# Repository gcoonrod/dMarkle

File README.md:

<!--
 dMarkle (c) by Greg Coonrod
 
 dMarkle is licensed under a
 Creative Commons Attribution-ShareAlike 4.0 International License.
 
 You should have received a copy of the license along with this
 work. If not, see <http://creativecommons.org/licenses/by-sa/4.0/>.
-->

# dMarkle

A Raspberry Pi Pico based dice rolling toy.

## Usage

The dMarkle is programmed to roll one of any d4, d6, d8, d10, d12, d20, or d100 dice. The rotary encoder can be turned to select the die and then pushed to roll.

## Schematic and PCB

- Current [Schematic](./dMarkle-schematic-rev0.1.pdf)
- Current [PCB](./dMarkle-board-rev0.1.pdf)
  - The Pi Pico will be mounted on pin sockets. Hence the components that would otherwise be in an exclusion zone.

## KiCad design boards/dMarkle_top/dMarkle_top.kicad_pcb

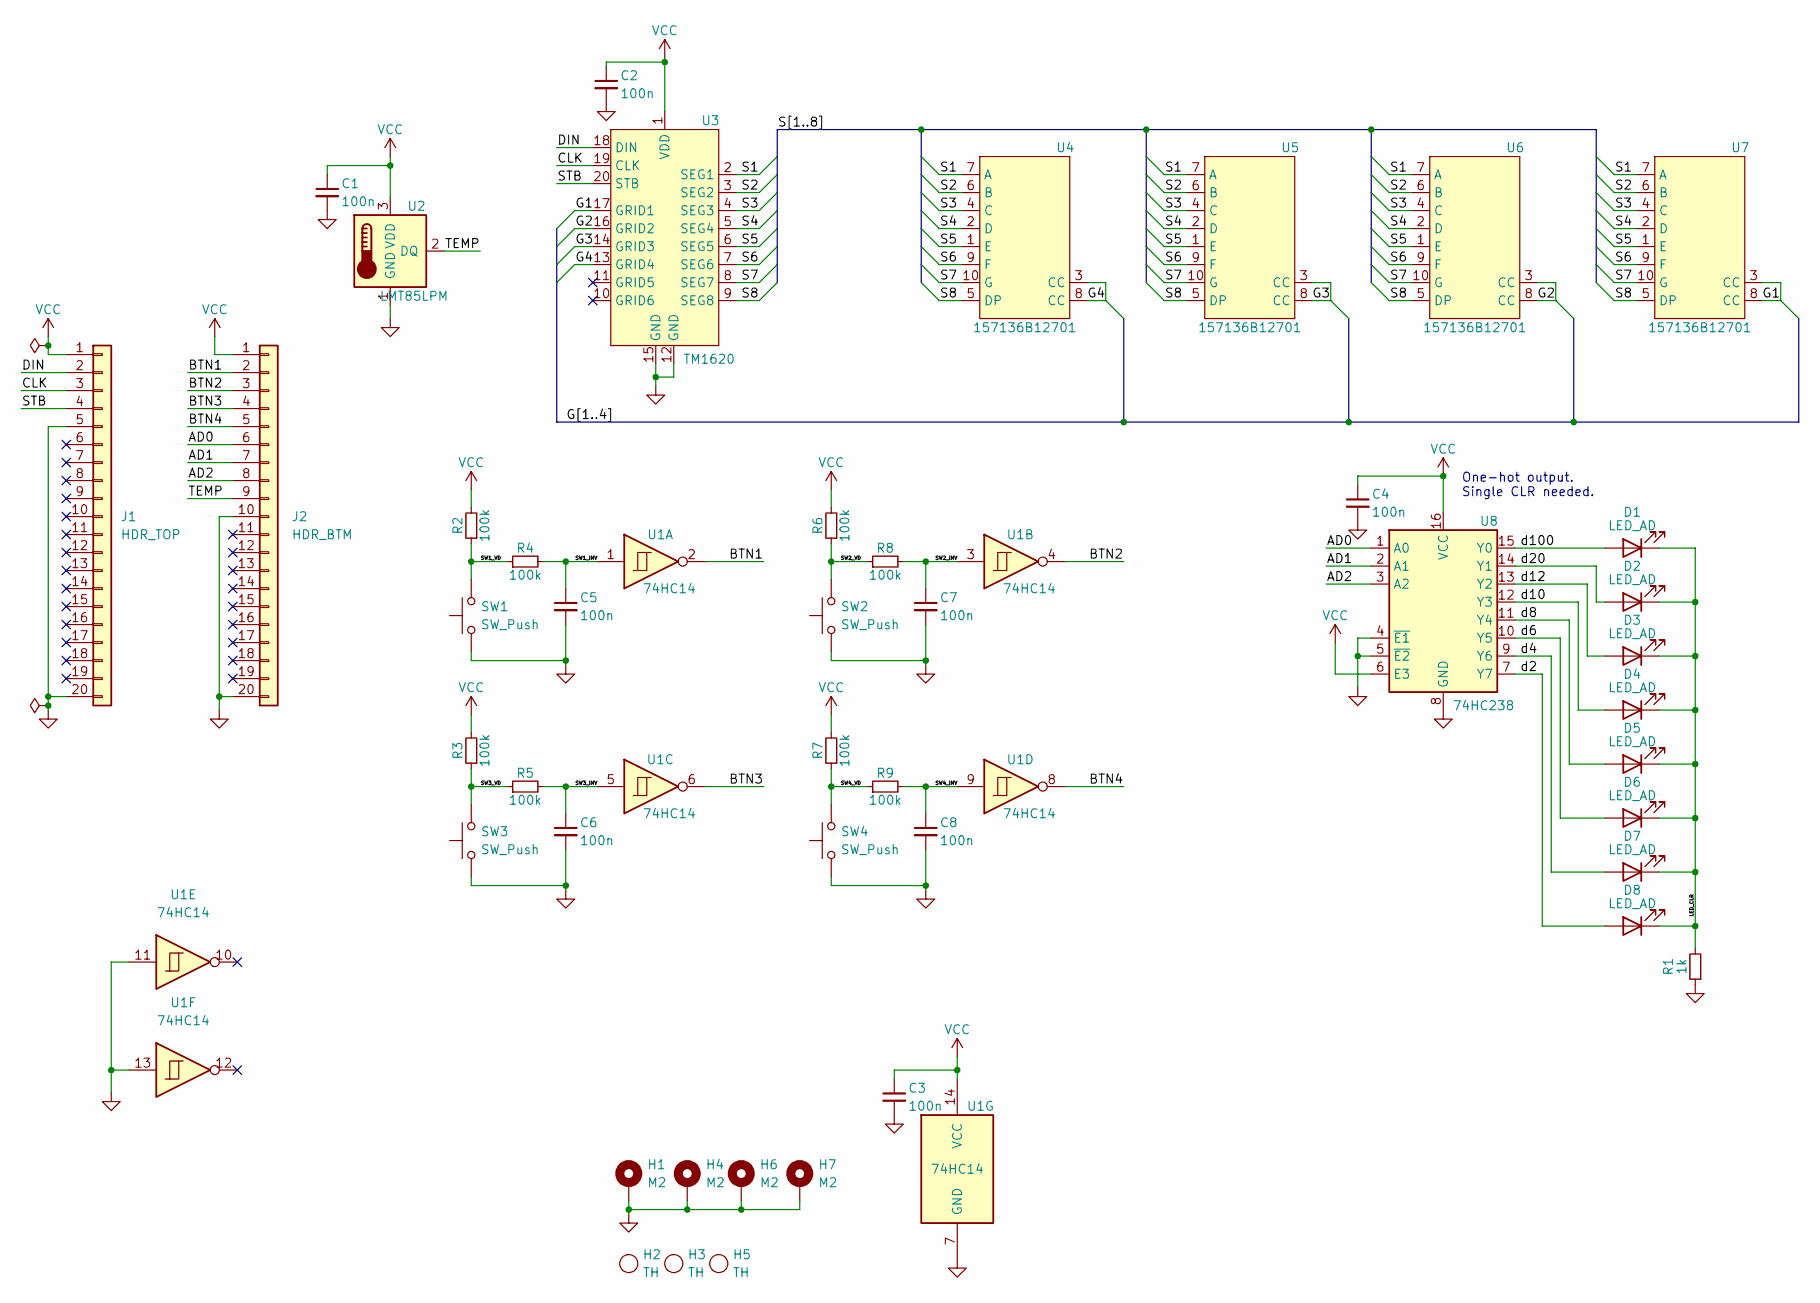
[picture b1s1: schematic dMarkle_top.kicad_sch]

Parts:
C1, C2, C3, C4, C5, C6, C7, C8: 100n; C_0603_1608Metric; Mfr Part CC0603KRX7R9BB104
D1, D2, D3, D4, D5, D6, D7, D8: LED_AD; LED_0603_1608Metric; Mfr Part C2290
H1, H4, H6, H7: M2; MountingHole_2.2mm_M2_Pad
H2, H3, H5: TH; ToolingHole
J1: HDR_TOP; PinHeader_1x20_P2.54mm_Vertical; Mfr Part 10129378-920001BLF
J2: HDR_BTM; PinHeader_1x20_P2.54mm_Vertical; Mfr Part M20-7822046
R1: 1k; R_0603_1608Metric; Mfr Part 0603WAF1001T5E
R2, R3, R4, R5, R6, R7, R8, R9: 100k; R_0603_1608Metric; Mfr Part 0603WAF1003T5E
SW1, SW2, SW3, SW4: SW_Push; SW_PUSH_6mm; Mfr Part TS02-66-73-BK-260-SCR-D
U1: 74HC14; DIP-14_W7.62mm_LongPads; Mfr Part TC74HC14APF
U2: LMT85LPM; TO-92_Inline; Mfr Part LMT85LPM
U3: TM1620; SOIC-20W_7.5x12.8mm_P1.27mm; Mfr Part TM1620
U4, U5, U6, U7: 157136B12701; Mfr Part 157136B12701
U8: 74HC238; DIP-16_W7.62mm_LongPads; Mfr Part CD74HC238E

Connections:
/AD0: J2.6, U8.1 (A0)
/AD1: J2.7, U8.2 (A1)
/AD2: J2.8, U8.3 (A2)
/BTN1: J2.2, U1.2
/BTN2: J2.3, U1.4
/BTN3: J2.4, U1.6
/BTN4: J2.5, U1.8
/CLK: J1.3, U3.19 (CLK)
/DIN: J1.2, U3.18 (DIN)
/G1: U3.17 (GRID1), U7.3 (CC), U7.8 (CC)
/G2: U3.16 (GRID2), U6.3 (CC), U6.8 (CC)
/G3: U3.14 (GRID3), U5.3 (CC), U5.8 (CC)
/G4: U3.13 (GRID4), U4.3 (CC), U4.8 (CC)
/LED_CLR: D1.1 (K), D2.1 (K), D3.1 (K), D4.1 (K), D5.1 (K), D6.1 (K), D7.1 (K), D8.1 (K), R1.2
/S1: U3.2 (SEG1), U4.7 (A), U5.7 (A), U6.7 (A), U7.7 (A)
/S2: U3.3 (SEG2), U4.6 (B), U5.6 (B), U6.6 (B), U7.6 (B)
/S3: U3.4 (SEG3), U4.4 (C), U5.4 (C), U6.4 (C), U7.4 (C)
/S4: U3.5 (SEG4), U4.2 (D), U5.2 (D), U6.2 (D), U7.2 (D)
/S5: U3.6 (SEG5), U4.1 (E), U5.1 (E), U6.1 (E), U7.1 (E)
/S6: U3.7 (SEG6), U4.9 (F), U5.9 (F), U6.9 (F), U7.9 (F)
/S7: U3.8 (SEG7), U4.10 (G), U5.10 (G), U6.10 (G), U7.10 (G)
/S8: U3.9 (SEG8), U4.5 (DP), U5.5 (DP), U6.5 (DP), U7.5 (DP)
/STB: J1.4, U3.20 (STB)
/SW1_INV: C5.1, R4.2, U1.1
/SW1_VD: R2.1, R4.1, SW1.2
/SW2_INV: C7.1, R8.2, U1.3
/SW2_VD: R6.1, R8.1, SW2.2
/SW3_INV: C6.1, R5.2, U1.5
/SW3_VD: R3.1, R5.1, SW3.2
/SW4_INV: C8.1, R9.2, U1.9
/SW4_VD: R7.1, R9.1, SW4.2
/TEMP: J2.9, U2.2 (DQ)
/d2: D8.2 (A), U8.7 (Y7)
/d4: D7.2 (A), U8.9 (Y6)
/d6: D6.2 (A), U8.10 (Y5)
/d8: D5.2 (A), U8.11 (Y4)
/d10: D4.2 (A), U8.12 (Y3)
/d12: D3.2 (A), U8.13 (Y2)
/d20: D2.2 (A), U8.14 (Y1)
/d100: D1.2 (A), U8.15 (Y0)
GND: C1.2, C2.2, C3.2, C4.2, C5.2, C6.2, C7.2, C8.2, H1.1, H4.1, H6.1, H7.1, J1.5, J1.20, J2.10, J2.20, R1.1, SW1.1, SW2.1, SW3.1, SW4.1, U1.7 (GND), U1.11, U1.13, U2.1 (GND), U3.12 (GND), U3.15 (GND), U8.4 (~E1), U8.5 (~E2), U8.8 (GND)
VCC: C1.1, C2.1, C3.1, C4.1, J1.1, J2.1, R2.2, R3.2, R6.2, R7.2, U1.14 (VCC), U2.3 (VDD), U3.1 (VDD), U8.6 (E3), U8.16 (VCC)

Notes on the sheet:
One-hot output. Single CLR needed.

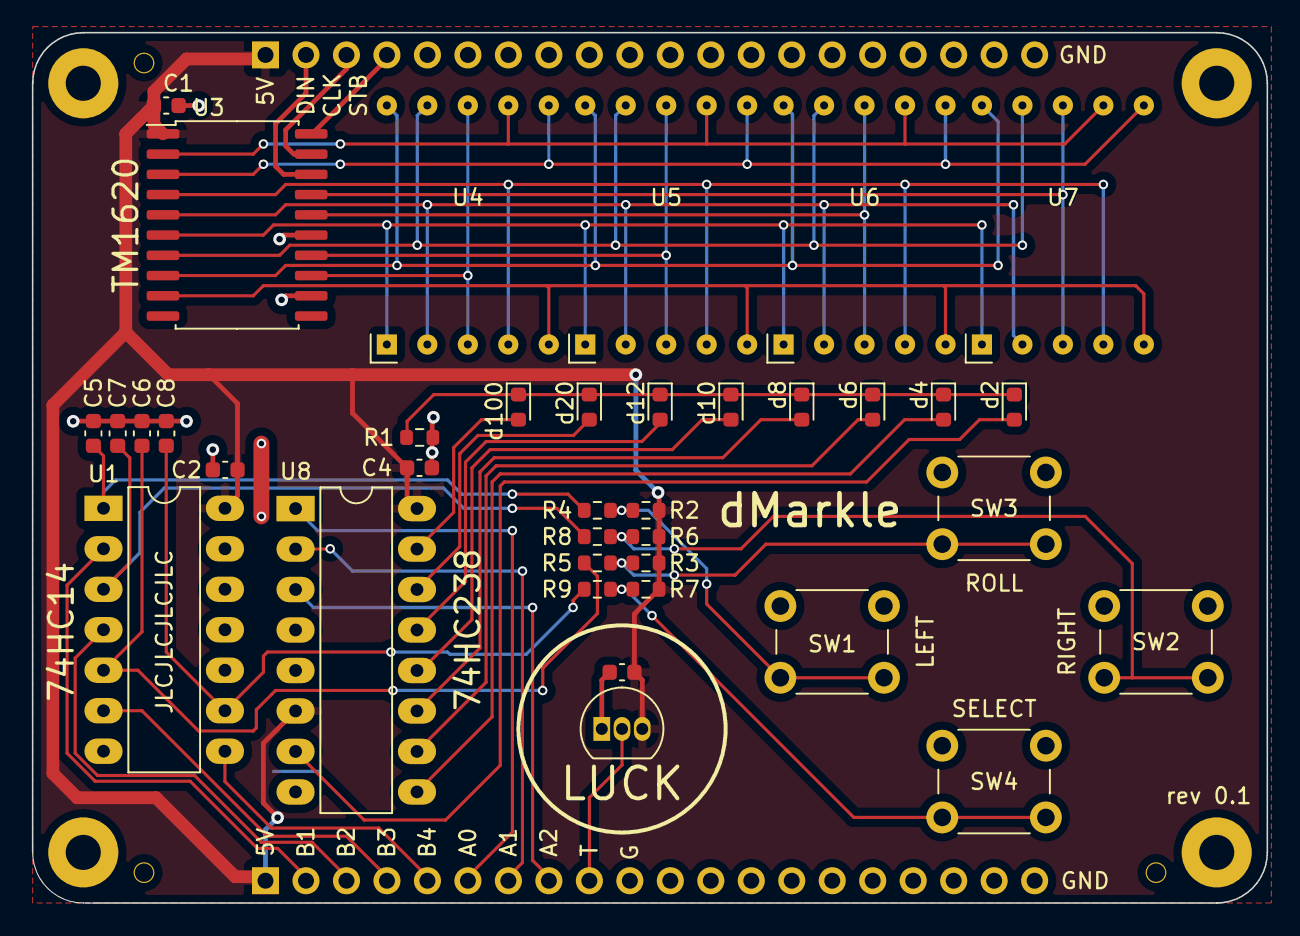
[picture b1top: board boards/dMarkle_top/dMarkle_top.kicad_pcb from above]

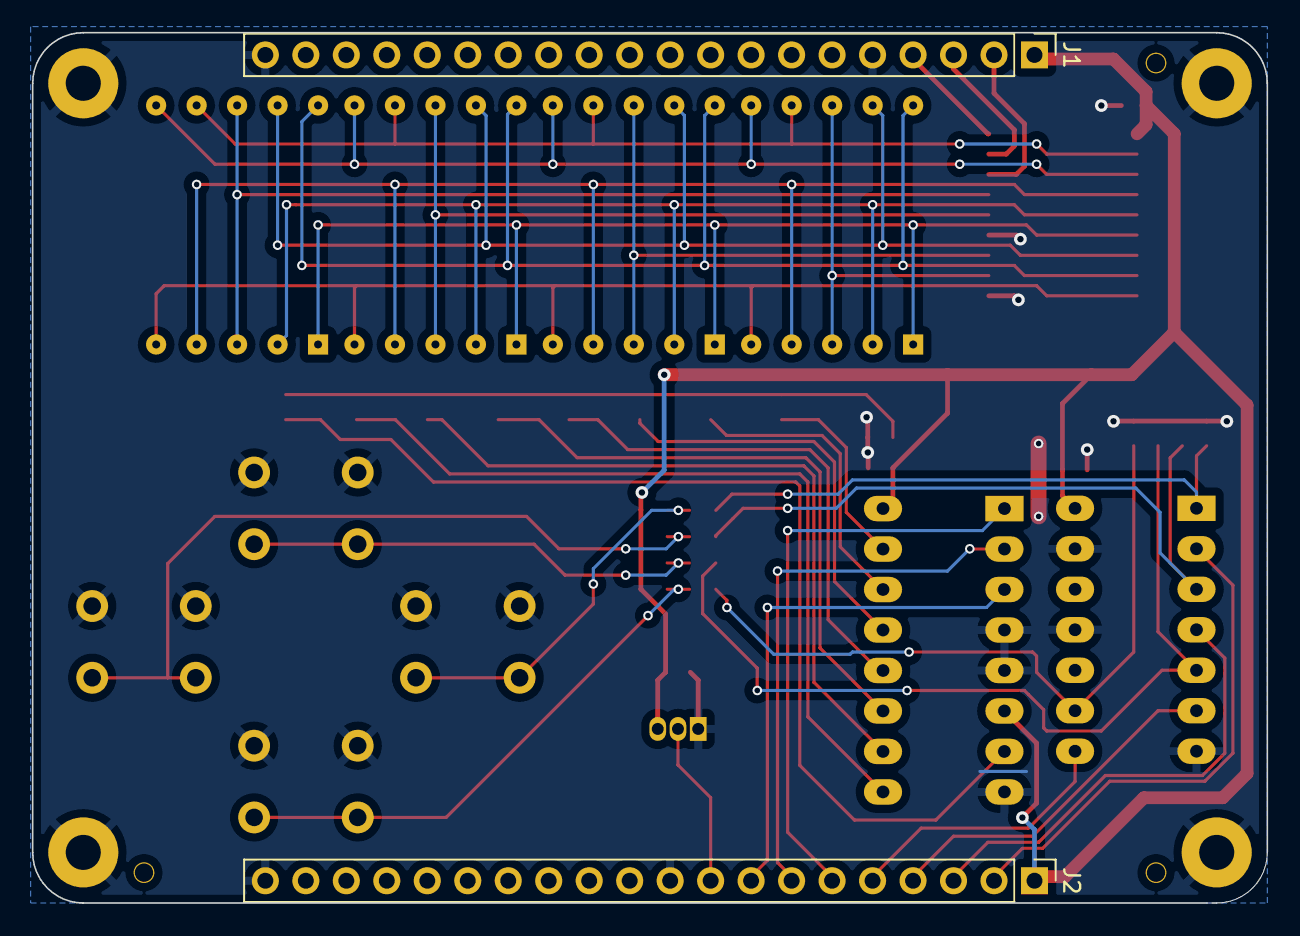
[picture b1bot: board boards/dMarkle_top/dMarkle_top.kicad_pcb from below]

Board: 2 copper layers, 77.5 x 54.6 mm, 46 parts (2 on the bottom side), 42 nets.

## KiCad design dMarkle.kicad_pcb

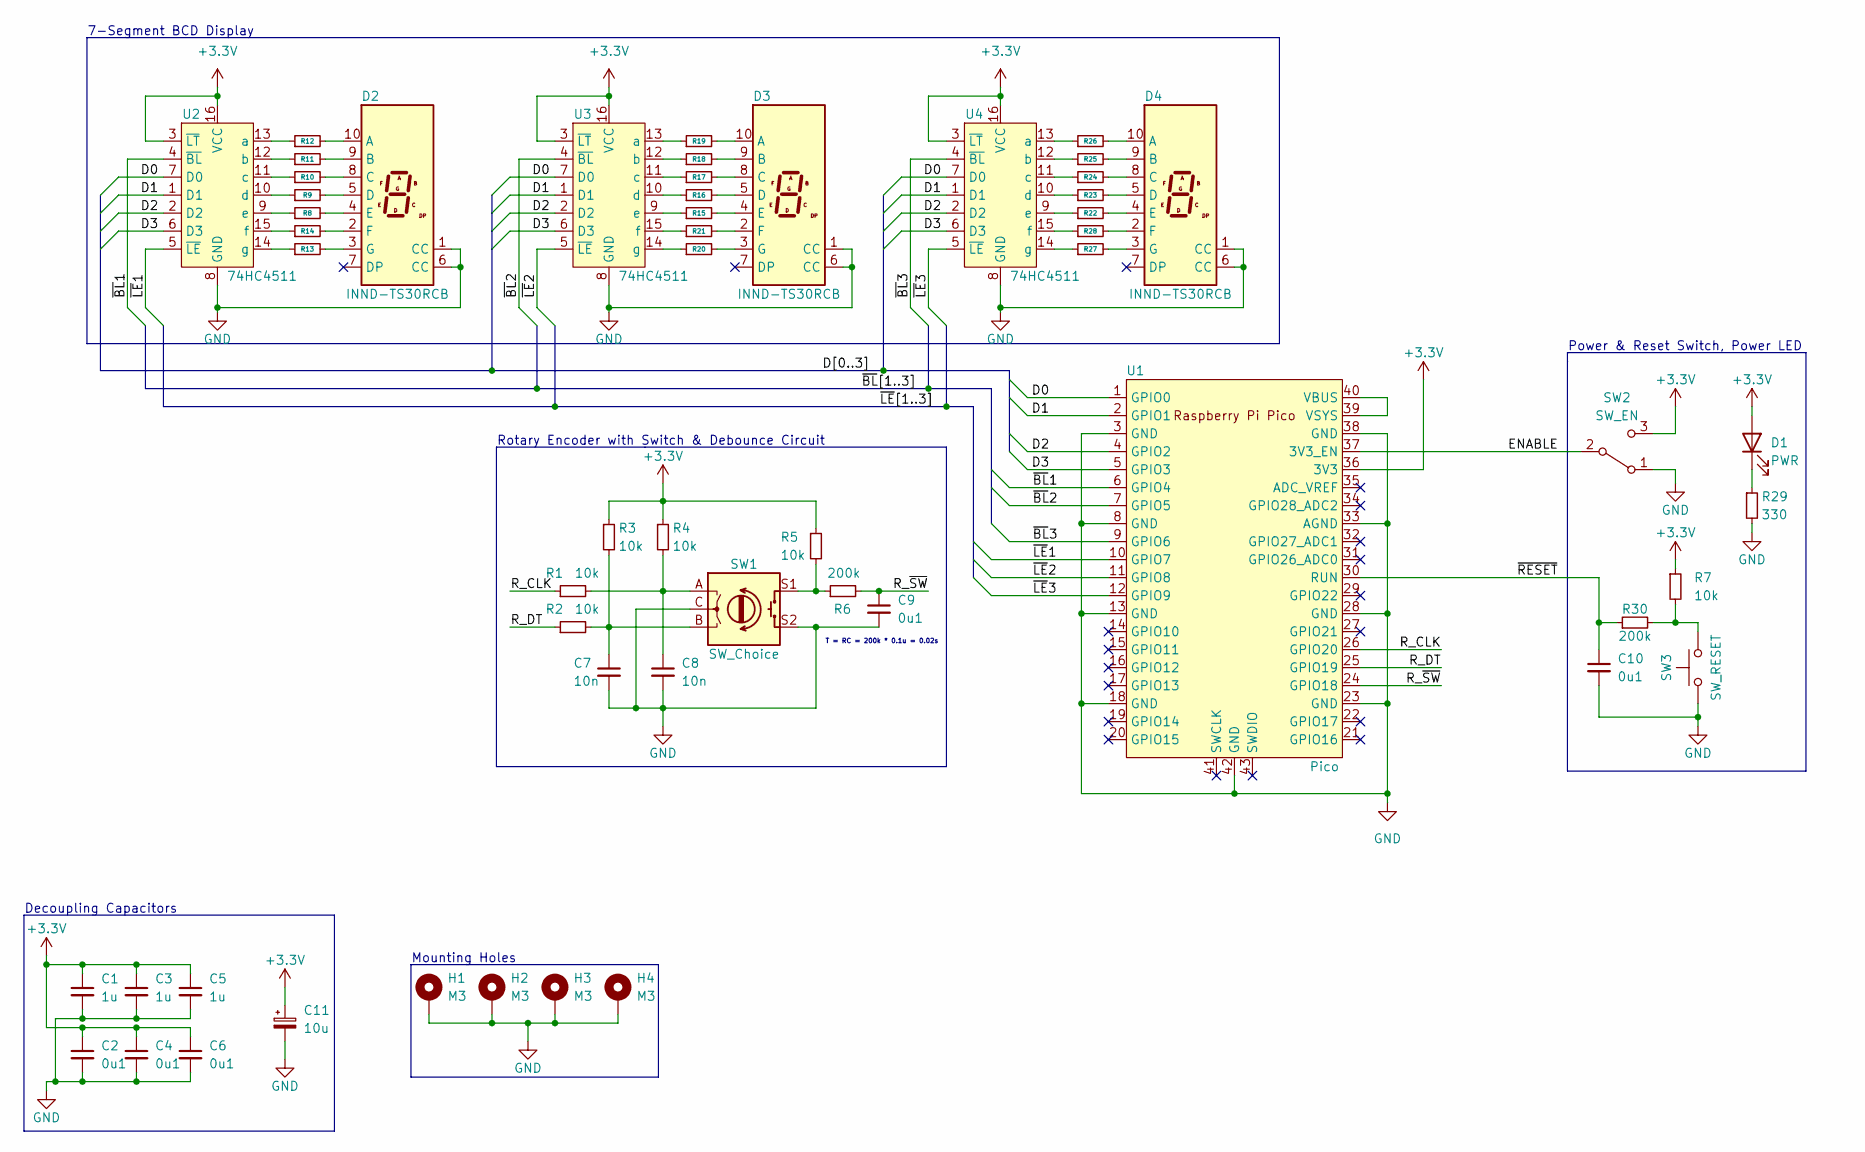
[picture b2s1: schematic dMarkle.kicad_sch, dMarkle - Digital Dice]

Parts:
C1, C3, C5: 1u; C_Rect_L4.0mm_W2.5mm_P2.50mm; Manufacturer Part Number FG18X5R1H105KRT06
C2, C4, C6, C9, C10: 0u1; C_Rect_L4.0mm_W2.5mm_P2.50mm; Manufacturer Part Number K104K15X7RF5TL2
C7, C8: 10n; C_Rect_L4.0mm_W2.5mm_P2.50mm; Manufacturer Part Number K103K15X7RF5TL2
C11: 10u; CP_Radial_D5.0mm_P2.00mm; Manufacturer Part Number 50YXM10MEFRTA5X11
D1: PWR; LED_D3.0mm; Manufacturer Part Number 151031SS04000
D2, D3, D4: INND-TS30RCB; HDSP-A151; Manufacturer Part Number INND-TS30RCB
H1, H2, H3, H4: M3; MountingHole_3.2mm_M3_Pad
R1, R2, R3, R4, R5, R7: 10k; R_Axial_DIN0204_L3.6mm_D1.6mm_P5.08mm_Horizontal; Manufacturer Part Number MBA02040C1002FRP00
R6, R30: 200k; R_Axial_DIN0204_L3.6mm_D1.6mm_P5.08mm_Horizontal; Manufacturer Part Number MBA02040C2003FCT00
R8, R9, R10, R11, R12, R13, R14, R15, R16, R17, R18, R19, R20, R21, R22, R23, R24, R25, R26, R27, R28, R29: 330; R_Axial_DIN0204_L3.6mm_D1.6mm_P5.08mm_Horizontal; Manufacturer Part Number MBA02040C3300FCT00
SW1: SW_Choice; RotaryEncoder_Alps_EC11E-Switch_Vertical_H20mm; Manufacturer Part Number PEC12R-4220F-S0024
SW2: SW_EN; SW_CuK_OS102011MA1QN1_SPDT_Angled; Manufacturer Part Number OS102011MA1QN1
SW3: SW_RESET; SW_PUSH_6mm; Manufacturer Part Number TL1105F160Q
U1: Pico; RPi_Pico_SMD_TH; Manufacturer Part Number SC0917
U2, U3, U4: 74HC4511; DIP-16_W7.62mm; Manufacturer Part Number CD74HC4511E

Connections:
+3.3V: C1.1, C2.1, C3.1, C4.1, C5.1, C6.1, C11.1, D1.2 (A), R3.1, R4.1, R5.1, R7.1, SW2.3 (C), U1.36 (3V3), U2.3 (~LT), U2.16 (VCC), U3.3 (~LT), U3.16 (VCC), U4.3 (~LT), U4.16 (VCC)
/D0: U1.1 (GPIO0), U2.7 (D0), U3.7 (D0), U4.7 (D0)
/D1: U1.2 (GPIO1), U2.1 (D1), U3.1 (D1), U4.1 (D1)
/D2: U1.4 (GPIO2), U2.2 (D2), U3.2 (D2), U4.2 (D2)
/D3: U1.5 (GPIO3), U2.6 (D3), U3.6 (D3), U4.6 (D3)
/ENABLE: SW2.2 (B), U1.37 (3V3_EN)
/R_CLK: R1.1, U1.26 (GPIO20)
/R_DT: R2.1, U1.25 (GPIO19)
/R_~SW: C9.1, R6.2, U1.24 (GPIO18)
/~BL1: U1.6 (GPIO4), U2.4 (~BL)
/~BL2: U1.7 (GPIO5), U3.4 (~BL)
/~BL3: U1.9 (GPIO6), U4.4 (~BL)
/~LE1: U1.10 (GPIO7), U2.5 (~LE)
/~LE2: U1.11 (GPIO8), U3.5 (~LE)
/~LE3: U1.12 (GPIO9), U4.5 (~LE)
/~RESET: C10.1, R30.1, U1.30 (RUN)
GND: C1.2, C2.2, C3.2, C4.2, C5.2, C6.2, C7.2, C8.2, C9.2, C10.2, C11.2, D2.1 (CC), D2.6 (CC), D3.1 (CC), D3.6 (CC), D4.1 (CC), D4.6 (CC), H1.1, H2.1, H3.1, H4.1, R29.2, SW1.C, SW1.S2, SW2.1 (A), SW3.1, U1.3 (GND), U1.8 (GND), U1.13 (GND), U1.18 (GND), U1.23 (GND), U1.28 (GND), U1.33 (AGND), U1.38 (GND), U1.42 (GND), U2.8 (GND), U3.8 (GND), U4.8 (GND)
unnamed: C7.1, R2.2, R3.2, SW1.B
unnamed: C8.1, R1.2, R4.2, SW1.A
unnamed: D1.1 (K), R29.1
unnamed: D2.2 (F), R14.2
unnamed: D2.3 (G), R13.2
unnamed: D2.4 (E), R8.2
unnamed: D2.5 (D), R9.2
unnamed: D2.8 (C), R10.2
unnamed: D2.9 (B), R11.2
unnamed: D2.10 (A), R12.2
unnamed: D3.2 (F), R21.2
unnamed: D3.3 (G), R20.2
unnamed: D3.4 (E), R15.2
unnamed: D3.5 (D), R16.2
unnamed: D3.8 (C), R17.2
unnamed: D3.9 (B), R18.2
unnamed: D3.10 (A), R19.2
unnamed: D4.2 (F), R28.2
unnamed: D4.3 (G), R27.2
unnamed: D4.4 (E), R22.2
unnamed: D4.5 (D), R23.2
unnamed: D4.8 (C), R24.2
unnamed: D4.9 (B), R25.2
unnamed: D4.10 (A), R26.2
unnamed: R5.2, R6.1, SW1.S1
unnamed: R8.1, U2.9 (e)
unnamed: R9.1, U2.10 (d)
unnamed: R10.1, U2.11 (c)
unnamed: R11.1, U2.12 (b)
unnamed: R12.1, U2.13 (a)
unnamed: R13.1, U2.14 (g)
unnamed: R14.1, U2.15 (f)
unnamed: R15.1, U3.9 (e)
unnamed: R16.1, U3.10 (d)
unnamed: R17.1, U3.11 (c)
unnamed: R18.1, U3.12 (b)
unnamed: R19.1, U3.13 (a)
unnamed: R20.1, U3.14 (g)
unnamed: R21.1, U3.15 (f)
unnamed: R22.1, U4.9 (e)
unnamed: R23.1, U4.10 (d)
unnamed: R24.1, U4.11 (c)
unnamed: R25.1, U4.12 (b)
unnamed: R26.1, U4.13 (a)
unnamed: R27.1, U4.14 (g)
unnamed: R28.1, U4.15 (f)
unnamed: R7.2, R30.2, SW3.2
unnamed: U1.39 (VSYS), U1.40 (VBUS)

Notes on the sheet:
Decoupling Capacitors
Rotary Encoder with Switch & Debounce Circuit
7-Segment BCD Display
T = RC = 200k * 0.1u = 0.02s
Mounting Holes
Power & Reset Switch, Power LED

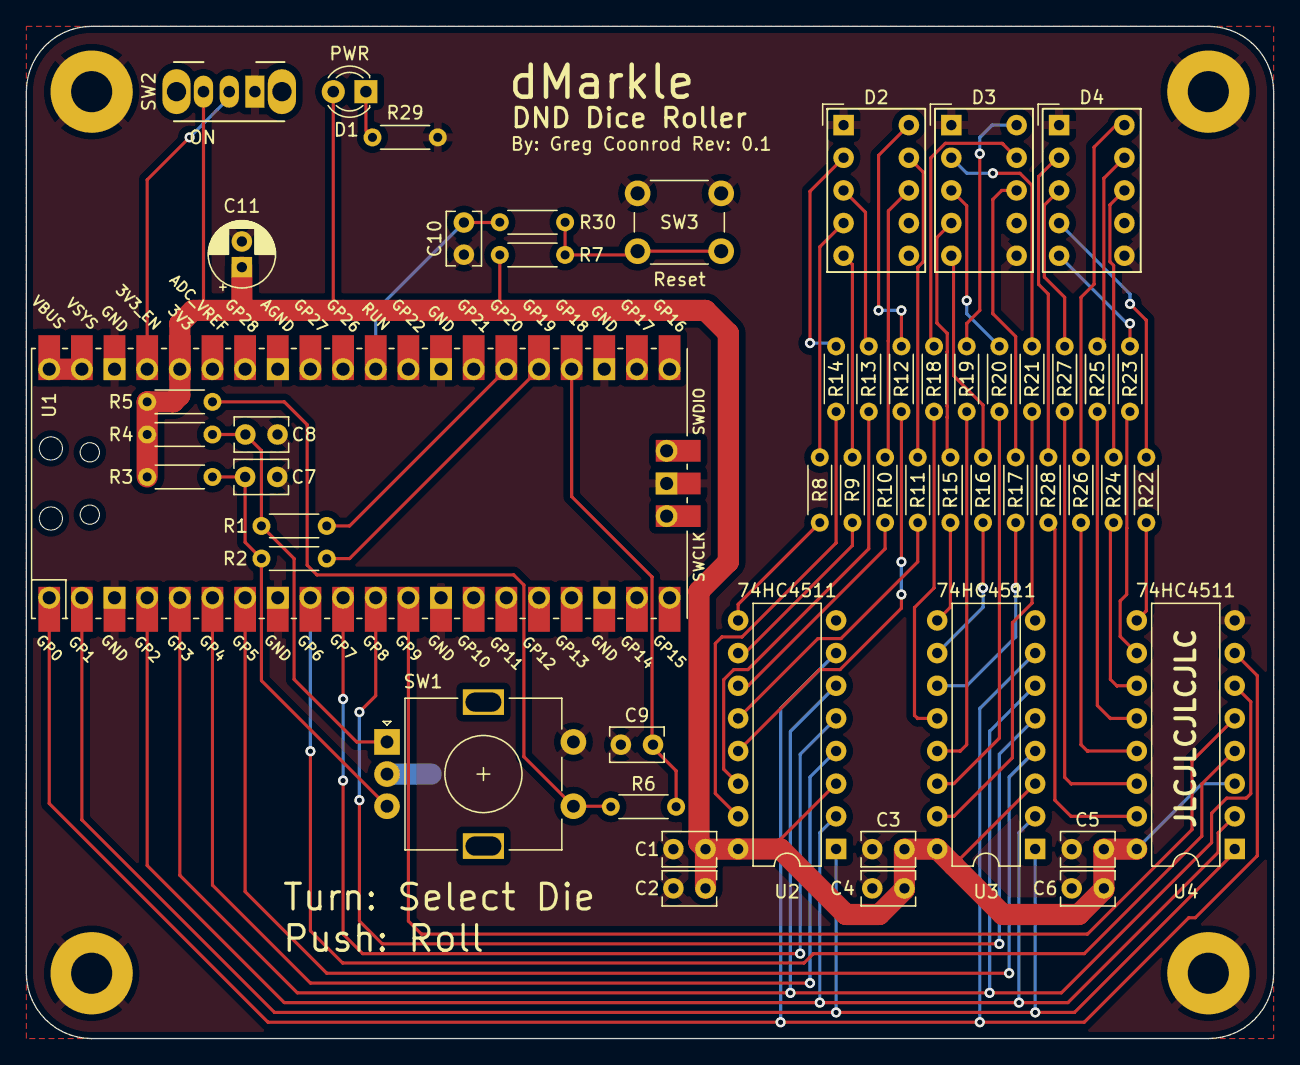
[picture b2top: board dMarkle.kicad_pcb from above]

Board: 2 copper layers, 97.0 x 78.7 mm, 56 parts (0 on the bottom side), 65 nets.

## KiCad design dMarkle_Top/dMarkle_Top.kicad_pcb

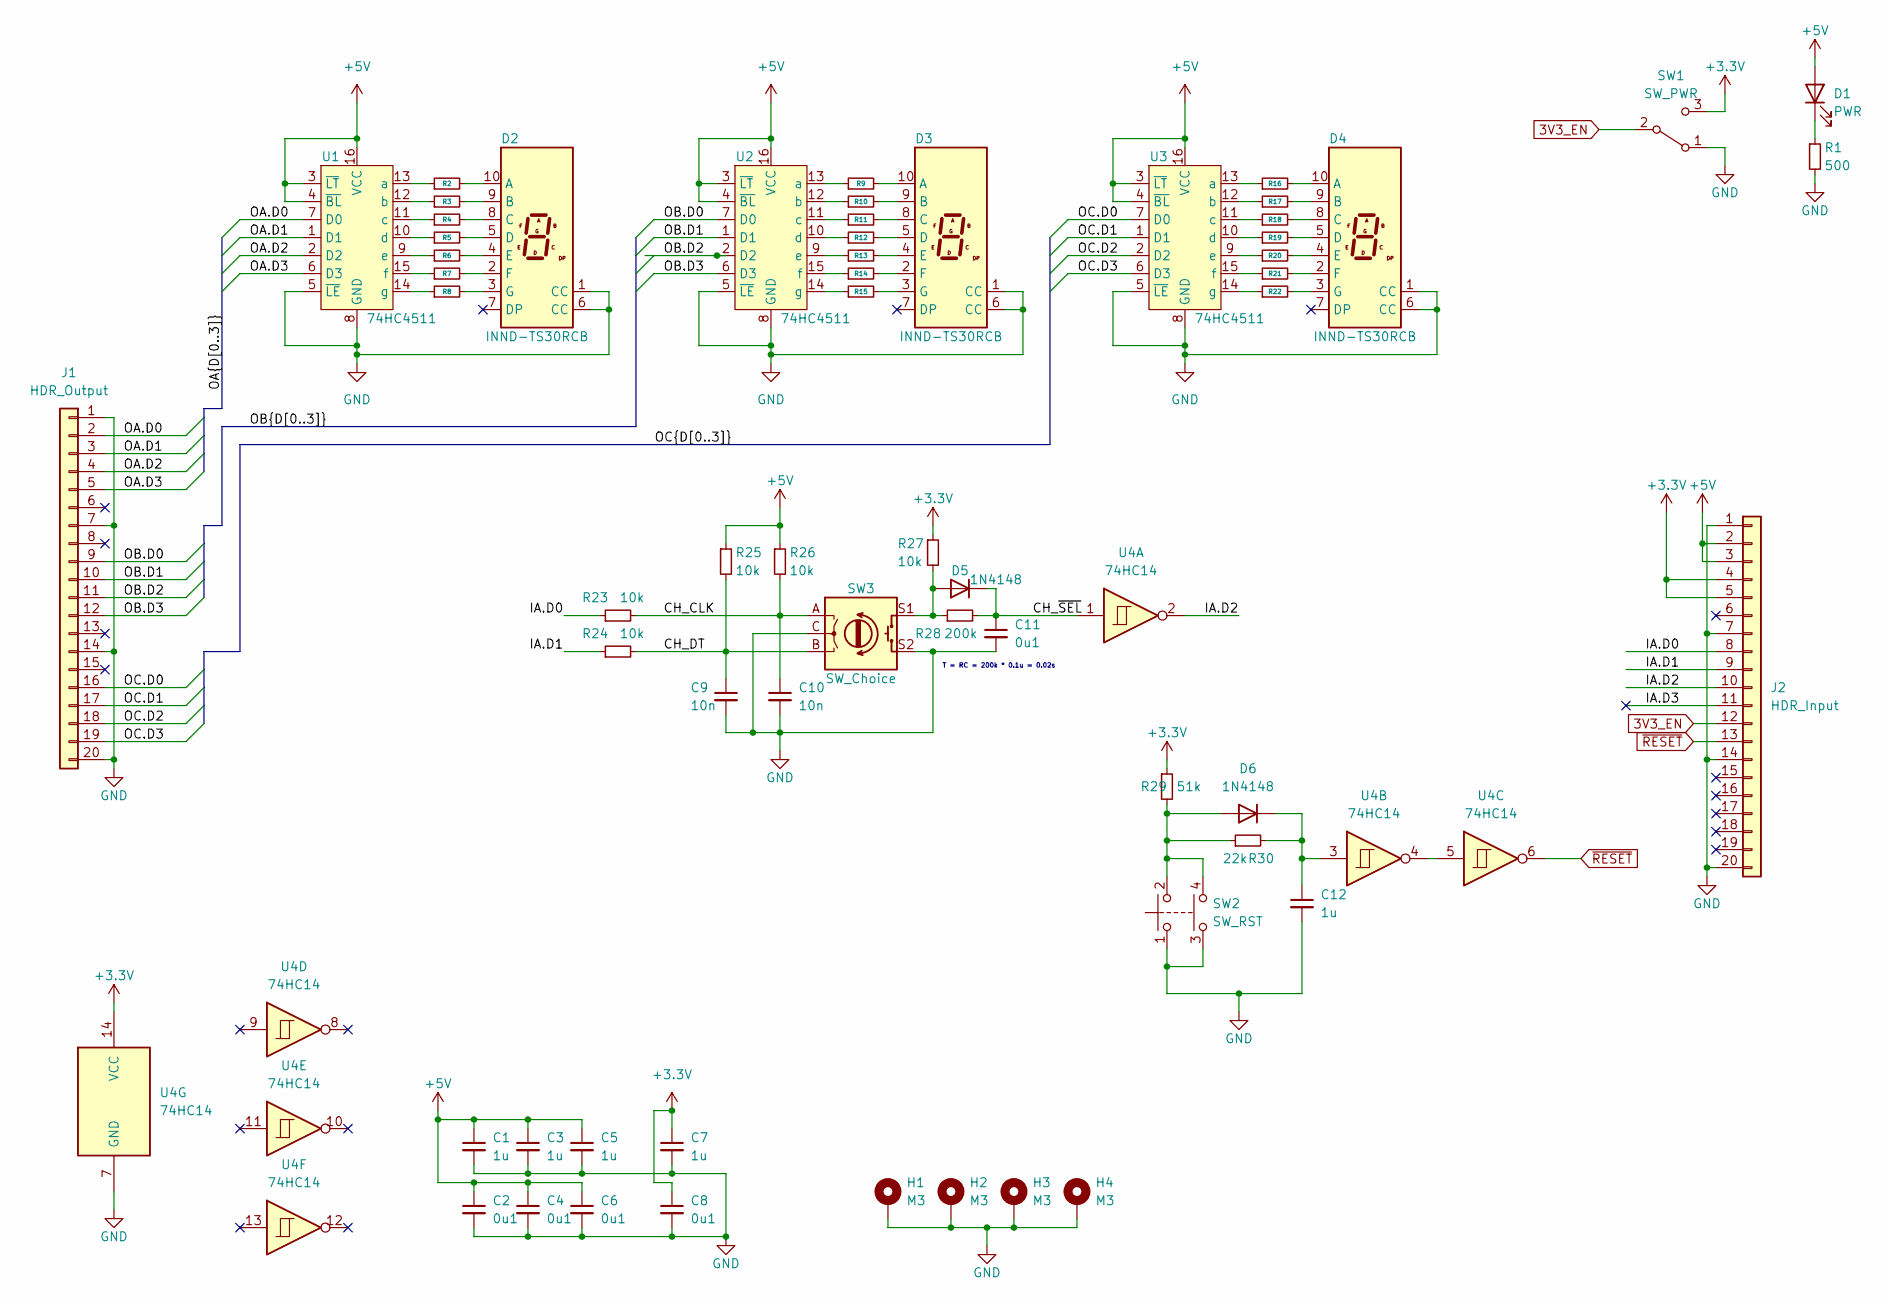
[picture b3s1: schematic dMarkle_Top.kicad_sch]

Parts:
C1, C3, C5, C7, C12: 1u; C_Rect_L4.0mm_W2.5mm_P2.50mm
C2, C4, C6, C8, C11: 0u1; C_Rect_L4.0mm_W2.5mm_P2.50mm
C9, C10: 10n; C_Rect_L4.0mm_W2.5mm_P2.50mm
D1: PWR; LED_D3.0mm
D2, D3, D4: INND-TS30RCB; HDSP-A151
D5, D6: 1N4148; D_DO-35_SOD27_P7.62mm_Horizontal
H1, H2, H3, H4: M3; MountingHole_3.2mm_M3_Pad
J1: HDR_Output; PinSocket_1x20_P2.54mm_Vertical
J2: HDR_Input; PinSocket_1x20_P2.54mm_Vertical
R1: 500; R_Axial_DIN0204_L3.6mm_D1.6mm_P5.08mm_Horizontal
R2, R3, R4, R5, R6, R7, R8, R9, R10, R11, R12, R13, R14, R15, R16, R17, R18, R19, R20, R21, R22: 330; R_Axial_DIN0204_L3.6mm_D1.6mm_P5.08mm_Horizontal
R23, R24, R25, R26, R27: 10k; R_Axial_DIN0204_L3.6mm_D1.6mm_P5.08mm_Horizontal
R28: 200k; R_Axial_DIN0204_L3.6mm_D1.6mm_P5.08mm_Horizontal
R29: 51k; R_Axial_DIN0204_L3.6mm_D1.6mm_P5.08mm_Horizontal
R30: 22k; R_Axial_DIN0204_L3.6mm_D1.6mm_P5.08mm_Horizontal
SW1: SW_PWR; SW_Slide_1P2T_CK_OS102011MS2Q
SW2: SW_RST; SW_Tactile_Straight_KSA0Axx1LFTR
SW3: SW_Choice; RotaryEncoder_Alps_EC11E-Switch_Vertical_H20mm; Manufacturer Part Number PEC12R-4220F-S0024
U1, U2, U3: 74HC4511; DIP-16_W7.62mm
U4: 74HC14; DIP-14_W7.62mm_Socket

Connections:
3V3_EN: J2.12, SW1.2 (B)
+5V: C1.1, C2.1, C3.1, C4.1, C5.1, C6.1, D1.2 (A), J2.2, J2.3, R25.1, R26.1, U1.3 (~LT), U1.4 (~BL), U1.16 (VCC), U2.3 (~LT), U2.4 (~BL), U2.16 (VCC), U3.3 (~LT), U3.4 (~BL), U3.16 (VCC)
/CH_CLK: C10.1, R23.2, R26.2, SW3.A
/CH_DT: C9.1, R24.2, R25.2, SW3.B
/CH_~SEL: C11.1, D5.1 (K), R28.2, U4.1
/IA.D0: J2.8, R23.1
/IA.D1: J2.9, R24.1
/IA.D2: J2.10, U4.2
/IA.D3: J2.11
/OA.D0: J1.2, U1.7 (D0)
/OA.D1: J1.3, U1.1 (D1)
/OA.D2: J1.4, U1.2 (D2)
/OA.D3: J1.5, U1.6 (D3)
/OB.D0: J1.9, U2.7 (D0)
/OB.D1: J1.10, U2.1 (D1)
/OB.D2: J1.11, U2.2 (D2)
/OB.D3: J1.12, U2.6 (D3)
/OC.D0: J1.16, U3.7 (D0)
/OC.D1: J1.17, U3.1 (D1)
/OC.D2: J1.18, U3.2 (D2)
/OC.D3: J1.19, U3.6 (D3)
GND: C1.2, C2.2, C3.2, C4.2, C5.2, C6.2, C7.2, C8.2, C9.2, C10.2, C11.2, C12.2, D2.1 (CC), D2.6 (CC), D3.1 (CC), D3.6 (CC), D4.1 (CC), D4.6 (CC), H1.1, H2.1, H3.1, H4.1, J1.1, J1.7, J1.14, J1.20, J2.1, J2.7, J2.14, J2.20, R1.2, SW1.1 (A), SW2.1, SW2.3, SW3.C, SW3.S2, U1.5 (~LE), U1.8 (GND), U2.5 (~LE), U2.8 (GND), U3.5 (~LE), U3.8 (GND), U4.7 (GND)
unnamed: D1.1 (K), R1.1
unnamed: D2.2 (F), R7.2
unnamed: D2.3 (G), R8.2
unnamed: D2.4 (E), R6.2
unnamed: D2.5 (D), R5.2
unnamed: D2.8 (C), R4.2
unnamed: D2.9 (B), R3.2
unnamed: D2.10 (A), R2.2
unnamed: D3.2 (F), R14.2
unnamed: D3.3 (G), R15.2
unnamed: D3.4 (E), R13.2
unnamed: D3.5 (D), R12.2
unnamed: D3.8 (C), R11.2
unnamed: D3.9 (B), R10.2
unnamed: D3.10 (A), R9.2
unnamed: D4.2 (F), R21.2
unnamed: D4.3 (G), R22.2
unnamed: D4.4 (E), R20.2
unnamed: D4.5 (D), R19.2
unnamed: D4.8 (C), R18.2
unnamed: D4.9 (B), R17.2
unnamed: D4.10 (A), R16.2
unnamed: D5.2 (A), R27.2, R28.1, SW3.S1
unnamed: D6.2 (A), R29.2, R30.1, SW2.2, SW2.4
unnamed: R6.1, U1.9 (e)
unnamed: R5.1, U1.10 (d)
unnamed: R4.1, U1.11 (c)
unnamed: R3.1, U1.12 (b)
unnamed: R2.1, U1.13 (a)
unnamed: R8.1, U1.14 (g)
unnamed: R7.1, U1.15 (f)
unnamed: R13.1, U2.9 (e)
unnamed: R12.1, U2.10 (d)
unnamed: R11.1, U2.11 (c)
unnamed: R10.1, U2.12 (b)
unnamed: R9.1, U2.13 (a)
unnamed: R15.1, U2.14 (g)
unnamed: R14.1, U2.15 (f)
unnamed: R20.1, U3.9 (e)
unnamed: R19.1, U3.10 (d)
unnamed: R18.1, U3.11 (c)
unnamed: R17.1, U3.12 (b)
unnamed: R16.1, U3.13 (a)
unnamed: R22.1, U3.14 (g)
unnamed: R21.1, U3.15 (f)
unnamed: C12.1, D6.1 (K), R30.2, U4.3
unnamed: U4.4, U4.5
~RESET: J2.13, U4.6

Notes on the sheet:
T = RC = 200k * 0.1u = 0.02s

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
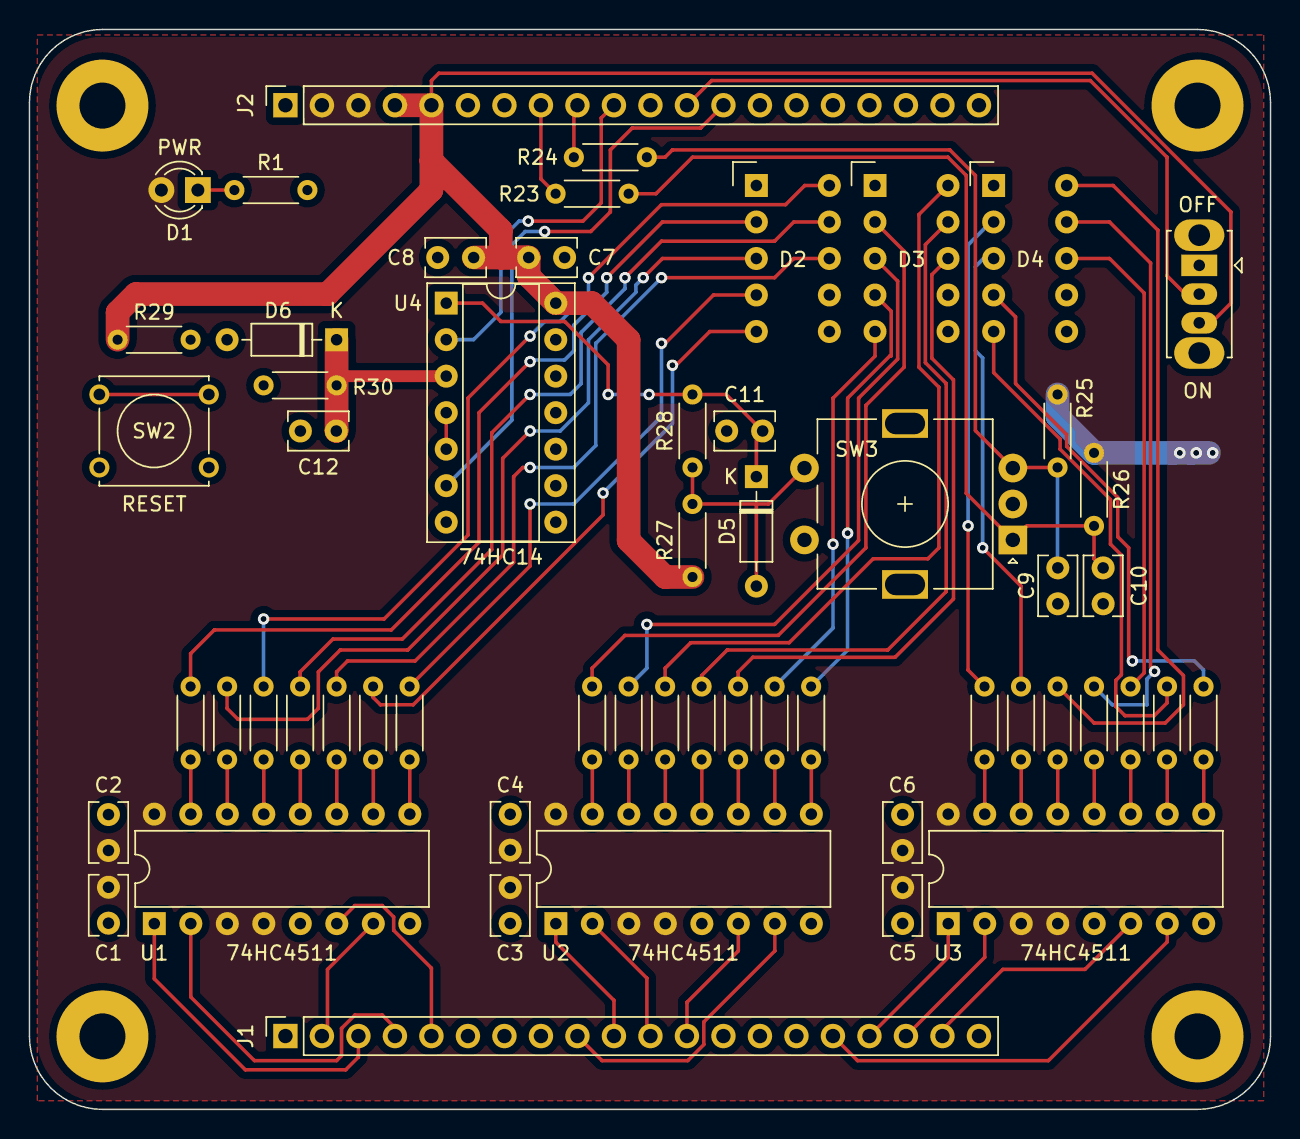
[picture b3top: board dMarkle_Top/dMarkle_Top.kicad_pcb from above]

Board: 2 copper layers, 86.4 x 75.1 mm, 61 parts (0 on the bottom side), 70 nets.

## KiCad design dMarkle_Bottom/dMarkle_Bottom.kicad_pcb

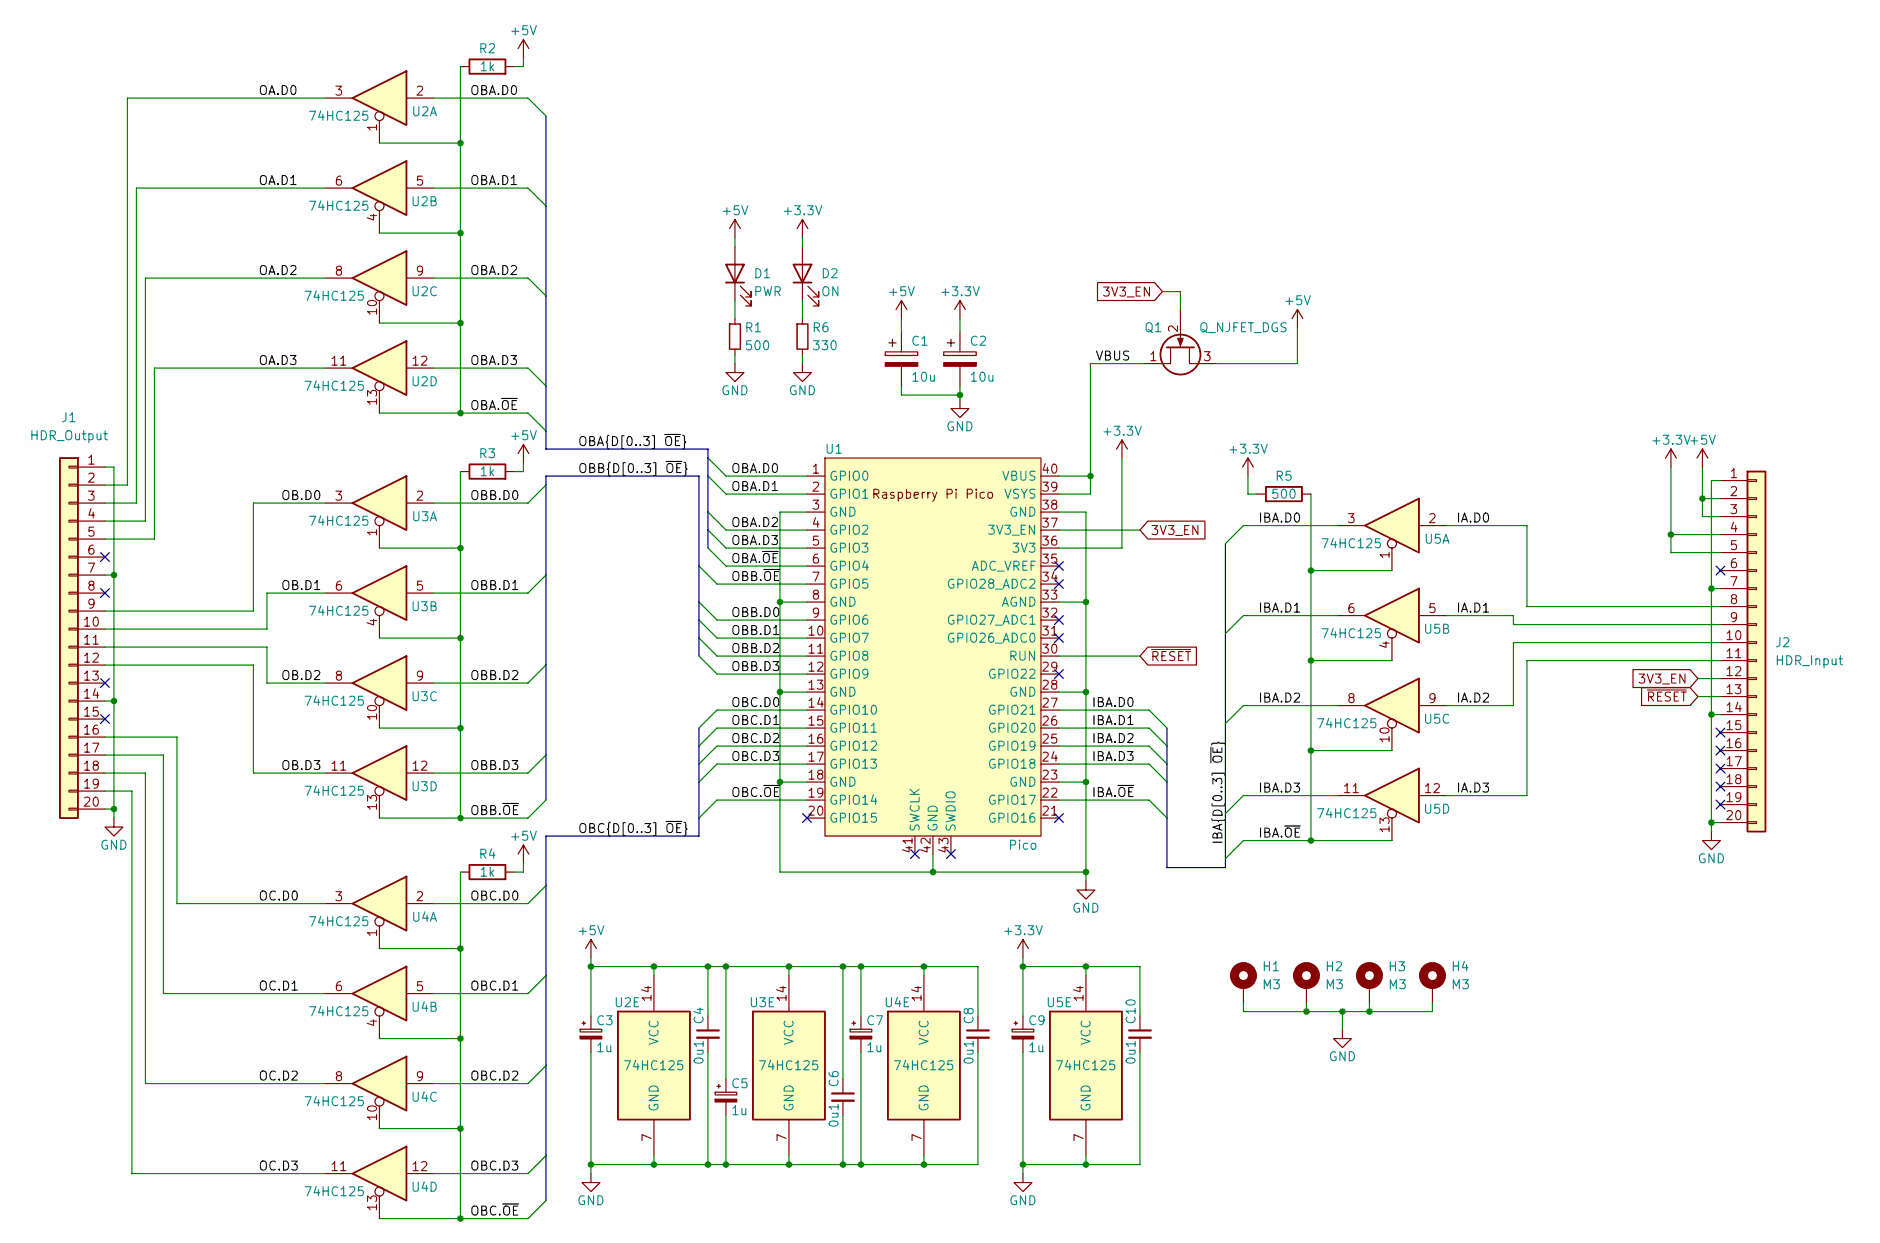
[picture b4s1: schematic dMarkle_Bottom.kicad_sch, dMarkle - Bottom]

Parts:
C1, C2: 10u; CP_Radial_D5.0mm_P2.00mm
C3, C5, C7, C9: 1u; C_Rect_L4.0mm_W2.5mm_P2.50mm
C4, C6, C8, C10: 0u1; C_Rect_L4.0mm_W2.5mm_P2.50mm
D1: PWR; LED_D3.0mm
D2: ON; LED_D3.0mm
H1, H2, H3, H4: M3; MountingHole_3.2mm_M3_Pad
J1: HDR_Output; PinSocket_1x20_P2.54mm_Vertical
J2: HDR_Input; PinSocket_1x20_P2.54mm_Vertical
Q1: Q_NJFET_DGS; TO-220-3_Horizontal_TabUp
R1, R5: 500; R_Axial_DIN0204_L3.6mm_D1.6mm_P5.08mm_Horizontal
R2, R3, R4: 1k; R_Axial_DIN0204_L3.6mm_D1.6mm_P5.08mm_Horizontal
R6: 330; R_Axial_DIN0204_L3.6mm_D1.6mm_P5.08mm_Horizontal
U1: Pico; RPi_Pico_SMD_TH
U2, U3, U4, U5: 74HC125; DIP-14_W7.62mm_Socket_LongPads

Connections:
3V3_EN: J2.12, Q1.2 (G), U1.37 (3V3_EN)
+3.3V: C2.1, C9.1, C10.1, D2.2 (A), J2.4, J2.5, R5.2, U1.36 (3V3), U5.14 (VCC)
+5V: C1.1, C3.1, C4.1, C5.1, C6.1, C7.1, C8.1, D1.2 (A), J2.2, J2.3, Q1.3 (S), R2.2, R3.2, R4.2, U2.14 (VCC), U3.14 (VCC), U4.14 (VCC)
/IA.D0: J2.8, U5.2
/IA.D1: J2.9, U5.5
/IA.D2: J2.10, U5.9
/IA.D3: J2.11, U5.12
/IBA.D0: U1.27 (GPIO21), U5.3
/IBA.D1: U1.26 (GPIO20), U5.6
/IBA.D2: U1.25 (GPIO19), U5.8
/IBA.D3: U1.24 (GPIO18), U5.11
/IBA.~OE: R5.1, U1.22 (GPIO17), U5.1, U5.4, U5.10, U5.13
/OA.D0: J1.2, U2.3
/OA.D1: J1.3, U2.6
/OA.D2: J1.4, U2.8
/OA.D3: J1.5, U2.11
/OB.D0: J1.9, U3.3
/OB.D1: J1.10, U3.6
/OB.D2: J1.11, U3.8
/OB.D3: J1.12, U3.11
/OBA.D0: U1.1 (GPIO0), U2.2
/OBA.D1: U1.2 (GPIO1), U2.5
/OBA.D2: U1.4 (GPIO2), U2.9
/OBA.D3: U1.5 (GPIO3), U2.12
/OBA.~OE: R2.1, U1.6 (GPIO4), U2.1, U2.4, U2.10, U2.13
/OBB.D0: U1.9 (GPIO6), U3.2
/OBB.D1: U1.10 (GPIO7), U3.5
/OBB.D2: U1.11 (GPIO8), U3.9
/OBB.D3: U1.12 (GPIO9), U3.12
/OBB.~OE: R3.1, U1.7 (GPIO5), U3.1, U3.4, U3.10, U3.13
/OBC.D0: U1.14 (GPIO10), U4.2
/OBC.D1: U1.15 (GPIO11), U4.5
/OBC.D2: U1.16 (GPIO12), U4.9
/OBC.D3: U1.17 (GPIO13), U4.12
/OBC.~OE: R4.1, U1.19 (GPIO14), U4.1, U4.4, U4.10, U4.13
/OC.D0: J1.16, U4.3
/OC.D1: J1.17, U4.6
/OC.D2: J1.18, U4.8
/OC.D3: J1.19, U4.11
/VBUS: Q1.1 (D), U1.39 (VSYS), U1.40 (VBUS)
GND: C1.2, C2.2, C3.2, C4.2, C5.2, C6.2, C7.2, C8.2, C9.2, C10.2, H1.1, H2.1, H3.1, H4.1, J1.1, J1.7, J1.14, J1.20, J2.1, J2.7, J2.14, J2.20, R1.2, R6.2, U1.3 (GND), U1.8 (GND), U1.13 (GND), U1.18 (GND), U1.23 (GND), U1.28 (GND), U1.33 (AGND), U1.38 (GND), U1.42 (GND), U2.7 (GND), U3.7 (GND), U4.7 (GND), U5.7 (GND)
unnamed: D1.1 (K), R1.1
unnamed: D2.1 (K), R6.1
~RESET: J2.13, U1.30 (RUN)
